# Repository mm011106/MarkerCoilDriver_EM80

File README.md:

> [!NOTE]
> 資料などについてコメント等あればDiscussionsに投稿ください。

# 機器名
## マーカコイルドライバ　EM-80D, EM-80R

# 機器の概要
マーカコイルドライバは、MEG計測時に被験者の頭部位置を推定するための信号を発生させる回路です。被験者の頭部に取り付けた小型コイル（マーカコイル）を既知の周波数で駆動し、発生した磁場をMEGで測定することで頭部位置を特定します。

# 構成 
<!-- この装置は、コイル駆動を行う（型式：EM-80D）とそれをコントロールするためのリモコン（型式：EM-80R）の2つの筐体に入った回路で構成されています。 </br>
コイル駆動回路は、MEG計測への電磁的影響を最小限にするためバッテリ（単３ｘ４）で駆動するように設計されています。また、リモコンはMEG装置と接続され、MEG装置からのコイル駆動動作のOn/Off操作を受け付けたり、MEG装置へコイルの駆動タイミング情報を送る役割を果たします。 </br>
両者はプラスティック光ファイバで接続され、シールドルーム外からの電磁的なノイズ流入を最小限に抑えます。 リモコン→コイル駆動回路への信号はパルス幅変調による1bitの情報で、EM-80Dの動作モードの変更を行います。コイル駆動回路→リモコンへの信号はコイル駆動のタイミング同期信号となっています。</br>
-->
この装置は、コイル駆動回路（型式：EM-80D）と、そのコントロール用リモコン（型式：EM-80R）の2つの筐体で構成されています。</br>
コイル駆動回路はシールドルーム内部に設置されるため、MEG計測への電磁的影響を最小限に抑える目的でバッテリ（単3×4）で駆動されます。</br>
リモコンはシールドルームの外でMEG装置と接続され、コイル駆動のOn/Off操作や駆動タイミング情報をMEG装置に送信します。</br>
両者はプラスチック光ファイバで接続され、シールドルーム外から電磁的ノイズの侵入を抑制します。</br>
リモコンからコイル駆動回路への信号はコイル駆動回路の動作モードを変更のためのパルス幅変調による1bitの情報です。一方、コイル駆動回路からリモコンへはコイル駆動タイミングの同期信号が送出されます。</br>
マーカコイルそのものについては、この設計情報に含まれません。

# 動作の概要
本装置は3つの状態があり、それぞれ「スタンバイモード」「80Hzモード」「ReTHMモード」と呼びます。

## スタンバイモード
スタンバイモードはコイルを駆動していない状態です。EM-80Dの電源スイッチを投入した直後の初期状態のモードになります。</br>
内部回路は動作しており、光ファイバを経由した外部からの動作指示を待ちます。

## 80Hzモード
5個のコイルをシーケンシャルに駆動するモードです。</br>
励磁の周波数は80Hzで、[このシーケンス](#コイル駆動のタイミングチャート)のようにコイルが駆動されます。シーケンスの最初に光ファイバ上に同期信号が出力され順次5個のコイルが駆動されます。</br>
コイルの駆動電流はEM-80Dのリアパネルにあるトグルスイッチ2つで設定できます。</br>

## ReTHMモード
5個のコイルをそれぞれ異なる周波数で同時に駆動するモードです。</br>
コイルの励磁周波数は、脳からの生体時期信号の周波数帯域から外れて高く設定されており、脳磁計測中にリアルタイムに頭部位置を検出するのに適しています。</br>
コイルの駆動電流はEM-80Dのリアパネルにあるトグルスイッチ2つで設定できます。

# 仕様
## EM-80D　マーカコイルドライバ （本体）
- ドライブコイル数：5
<br></br>
- 駆動電流 　(リアパネルスイッチによる　4点切り替え)
  - 5/10/50/100μAo-p 	（80Hzモード）
  - 3/6/10/20μAo-p　	（ReTHMモード）
<br></br>
- 動作モード （スタンバイモード/80Hzモード/ReTHMモード）
  - スタンバイモード</br>
    （コイル駆動なし）
<br></br>
  - 80Hzモード
    - 駆動波形：24波のバースト波による順次駆動（[下図参照](#コイル駆動のタイミングチャート)）
    - 駆動周波数：80Hz(typ)
<br></br>
  - ReTHMモード
    - 駆動波形：連続波
    - 駆動周波数 </br>
    CH0	20kHz </br>
    CH1	18kHz </br>
    CH2	16kHz </br>
    CH3	14kHz </br>
    CH4	12kHz
<br></br>

- 動作モード切替 </br>
    リモートコントローラEM-80Rからの信号による（光ファイバ経由）
<br></br>
- インターフェイス </br>
  プラスティック光ファイバ2本による（EM-80Rとの接続専用）
  - 入力信号：駆動モード切替
  - 出力信号：同期信号（80Hzモード時のみ）
<br></br>
- 操作：フロントパネルトグルスイッチによる電源のOn/Off
<br></br>
- 表示：電源電圧低下警告 Low-Battery（LED:赤）
<br></br>
- 電源：単三充電池（Ni-MH）4本
<br></br>
<br></br>
## EM-80R　リモートコントローラ
- 操作
  - フロントパネルトグルスイッチによる駆動モードの変更
  - 外部インターフェイスからの信号による駆動モードの変更
<br></br>
- 表示：LED（緑）によるEM-80Dの駆動モード表示 </br>
    　消灯　　スタンバイモード </br>
    　点滅　　80Hzモード動作中 </br>
    　点灯　　ReTHMモード動作中 </br>
<br></br>
- 外部（MEG装置）インターフェイス
  - 入力2bit（on命令、off命令　各1bit）
  - 出力1bit（同期信号）
  - コネクタ型式：HR10G-10R-10P（ヒロセ）（[ピンアサイン](#meg接続用コネクタピン配置)）
<br></br>
- 電源</br>
  - +5V、100mA以下（microUSBコネクタによる）
<br></br><br></br>
## 動作に必要なもの
- 単三充電池（Ni-MH）4本
- EM-80D ~ EM-80R間接続用光ファイバケーブル
- EM-80R用電源:　USB電源 (5V)もしくはパソコンのUSB端子 と USB-microケーブル
<br></br>

## コイル駆動のタイミングチャート
<!--  -->

## ブロック図
### EM-80D

</br>
</br>
</br>

### EM-80R

</br>
</br>
</br>

## MEG接続用コネクタ　ピン配置
- コネクタ型番：[HR10G-10R-10P73](https://www.hirose.com/ja/product/p/CL0110-1608-0-73#) ヒロセ（レセプタクル）

### MEG接続用コネクタのフォトカプラ周辺回路

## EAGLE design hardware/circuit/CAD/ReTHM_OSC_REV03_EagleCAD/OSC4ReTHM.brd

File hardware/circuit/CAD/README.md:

# このディレクトリについて
このディレクトリは回路図CADのプロジェクトが保管されています。</br>
使用したCADは　CadSoft Eagle バージョン7.4　です。</br>

## 構成
[本体](./EM-80DR_REV06_EagleCAD)のCADデータは、EM-80Dマーカコイルドライバ本体と、EM-80Rリモートコントローラの2つの設計が1つのプロジェクトとして登録されています。基板データは2つの設計が面付されています。</br>
本体回路のほかに、本体内部で使用するワイヤハーネスの設計図も入っています。

[ReTHM_OSC](./ReTHM_OSC_REV03_EagleCAD)のCADデータは、内蔵するReTHMモード用の発振回路の設計がプロジェクトとして登録されています。</br>
ReTHM発振回路は5種類の周波数設定があります。基板は同じで回路定数を変更して5種類の発振周波数を実現します。

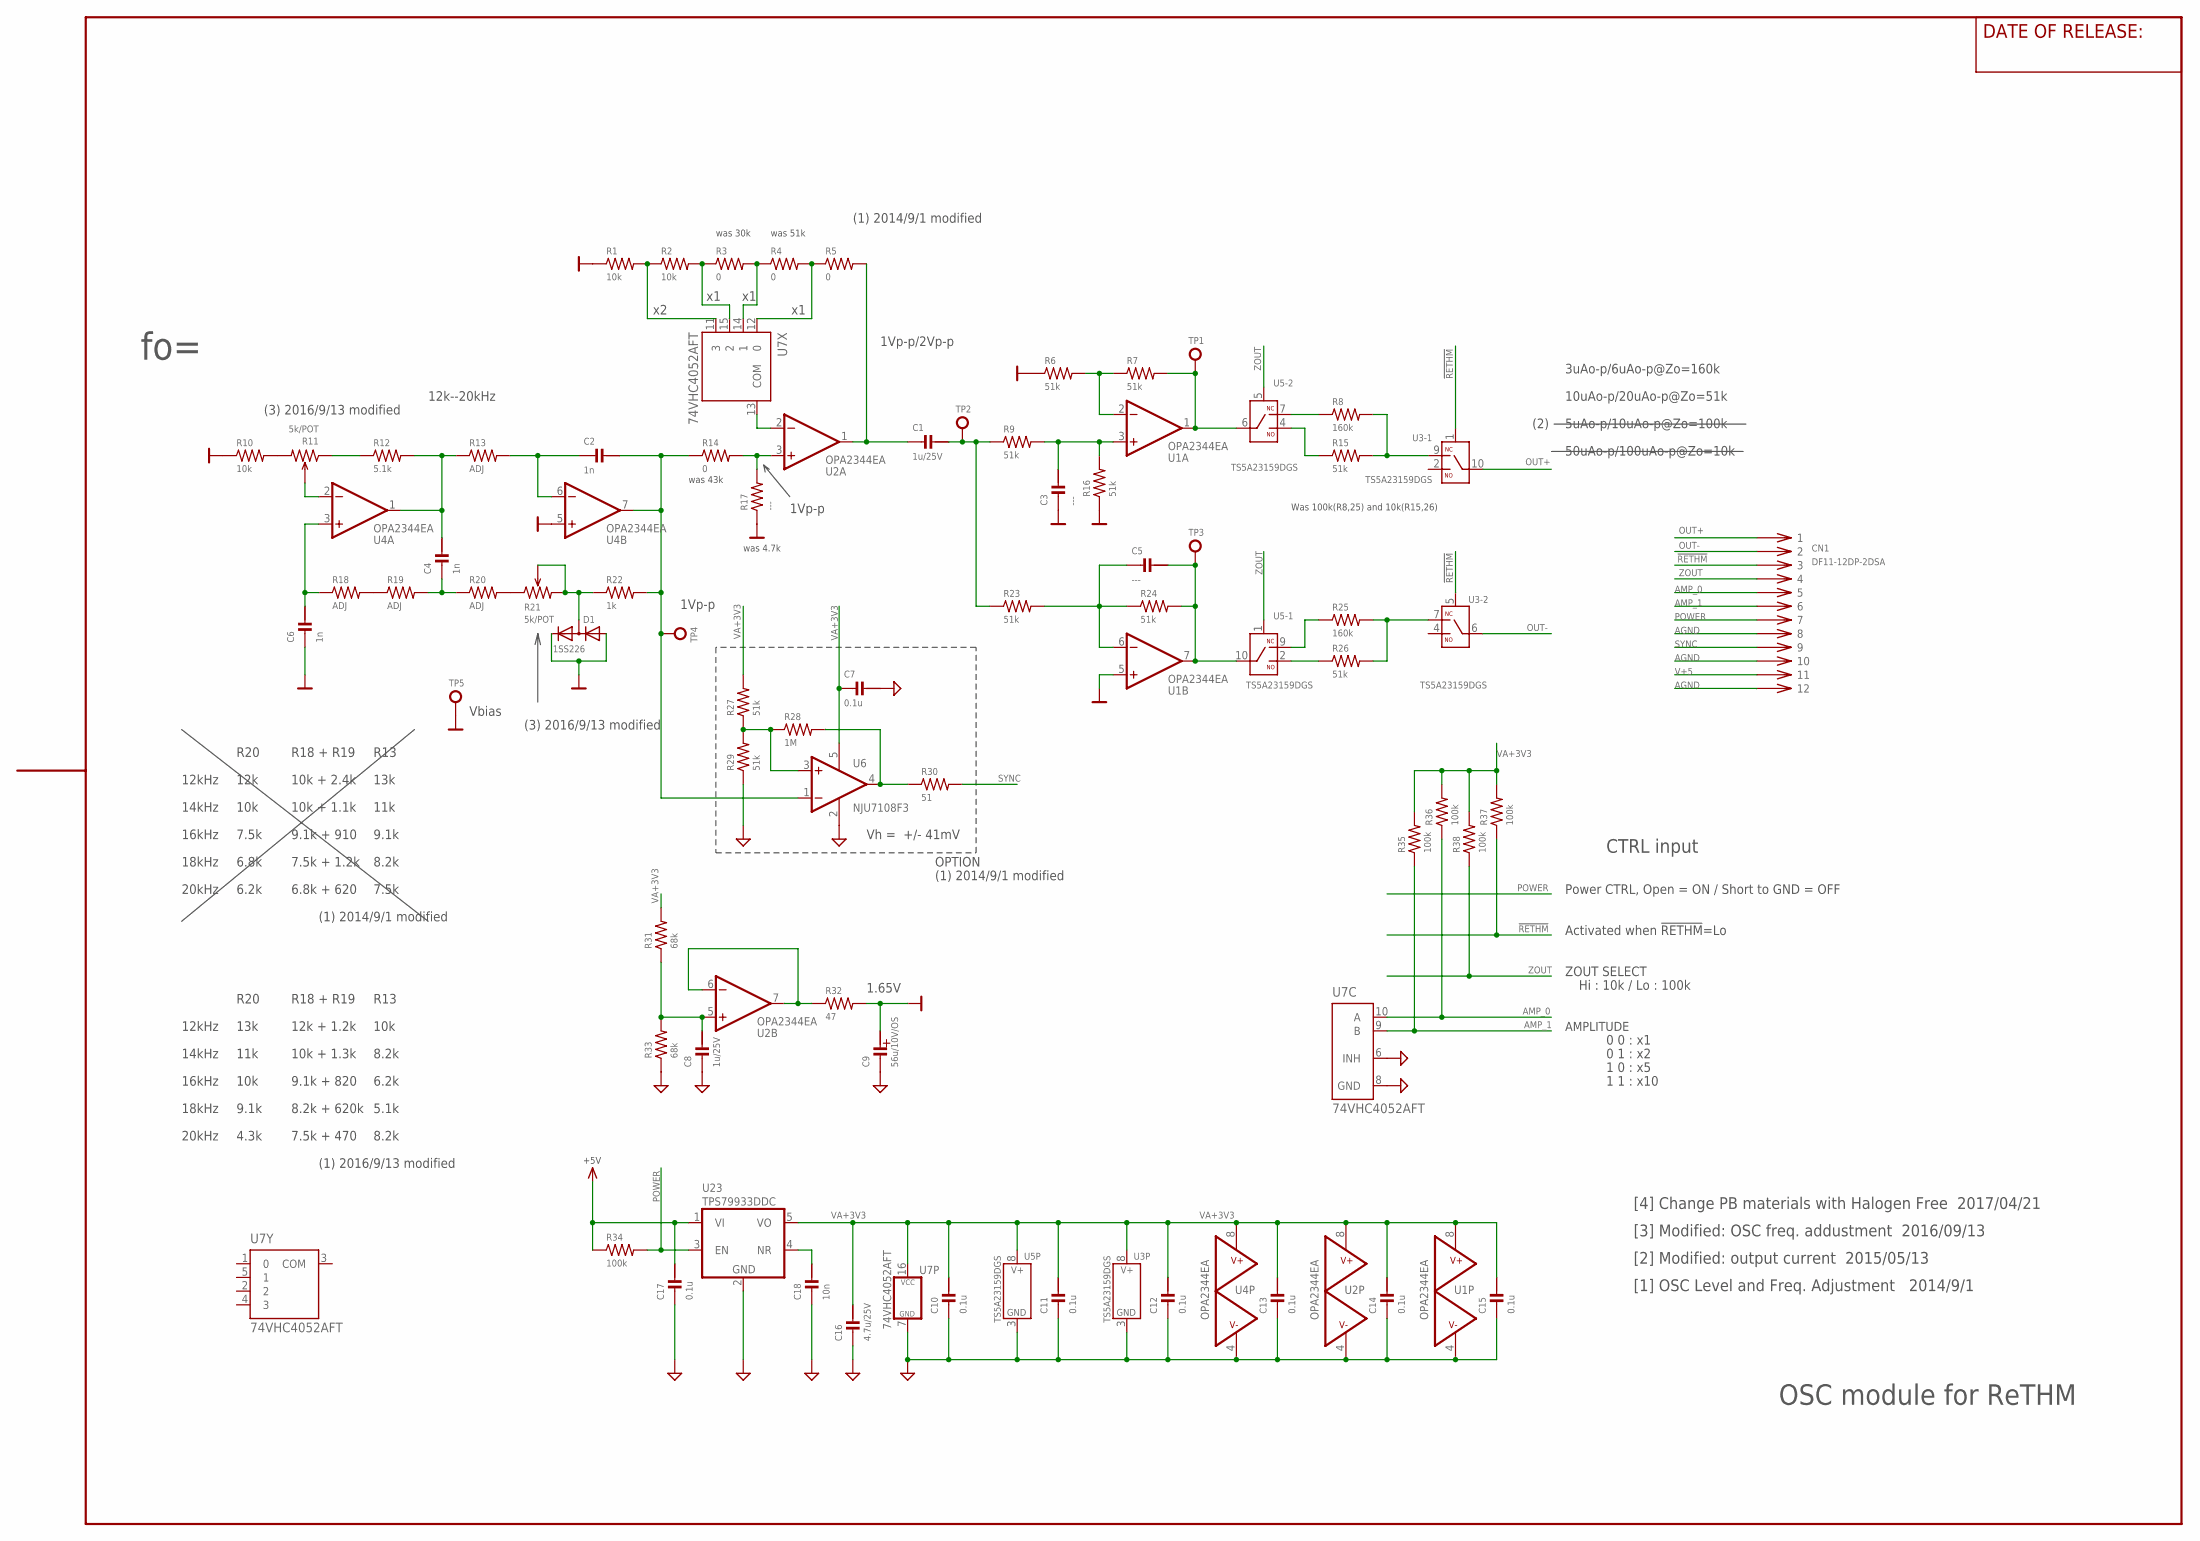
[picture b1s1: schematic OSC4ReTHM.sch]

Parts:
C1, C8: 1u/25V; CM1608
C2, C4, C6: 1n; CM2012
C3, C5: ---; CM2012
C7, C10, C11, C12, C13, C14, C15, C17: 0.1u; CM1608
C9: 56u/10V/OS; PHI_6.3
C16: 4.7u/25V; CM2012
C18: 10n; CM2012
CN1: DF11-12DP-2DSA
D1: 1SS226; SOT23
R1, R2, R10: 10k; RM1608
R3, R4, R5, R14: 0; RM1608
R6, R7, R9, R15, R16, R23, R24, R26, R27, R29: 51k; RM1608
R8, R25: 160k; RM1608
R11, R21: 5k/POT; CT-6
R12: 5.1k; RM1608
R13, R18, R19, R20: ADJ; RM1608
R17: ---; RM1608
R22: 1k; RM1608
R28: 1M; RM1608
R30: 51; RM1608
R31, R33: 68k; RM1608
R32: 47; RM1608
R34, R35, R36, R37, R38: 100k; RM1608
TP1, TP3, TP5: TP-1PAD; TP_PAD_1MM
TP2, TP4: TP-LC3G; TP_TH_0R9MM
U1, U2, U4: OPA2344EA; MSO8_AEL
U3, U5: TS5A23159DGS; MSOP10
U6: NJU7108F3; SC88A
U7: 74VHC4052AFT; TSSOP16-P-044-065A
U23: TPS79933DDC; SOT-23-5

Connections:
0V: C3.2, C6.2, C9.POS, D1.1 (A), D1.2 (C), R1.1, R6.1, R10.1, R16.1, R17.1, R32.2, TP5.P$1, U1.5 (+IN), U4.5 (+IN)
!RETHM: CN1.3, R37.1, U3.1 (IN), U3.5 (IN)
AGND: C7.1, C8.2, C9.NEG, C10.2, C11.2, C12.2, C13.2, C14.2, C15.2, C16.2, C17.2, C18.2, CN1.8, CN1.10, CN1.12, R29.1, R33.1, U1.4 (V-), U2.4 (V-), U3.3 (V-), U4.4 (V-), U5.3 (V-), U6.2 (V-), U7.6 (INH), U7.7 (GND), U7.8 (GND), U23.2 (GND)
AMP_0: CN1.5, R36.1, U7.10 (A)
AMP_1: CN1.6, R35.1, U7.9 (B)
unnamed: R20.2, R21.1
unnamed: R10.2, R11.3
unnamed: C18.1, U23.4 (NR)
unnamed: R1.2, R2.1, U7.11 (3)
unnamed: R2.2, R3.1, U7.15 (2)
unnamed: R3.2, R4.1, U7.14 (1)
unnamed: R4.2, R5.1, U7.12 (0)
unnamed: C8.1, R31.1, R33.2, U2.5 (+IN)
unnamed: C5.2, R23.2, R24.1, U1.6 (-IN)
unnamed: U2.2 (-IN), U7.13 (COM)
unnamed: C1.2, R5.2, U2.1 (OUT)
unnamed: R14.2, R17.2, U2.3 (+IN)
unnamed: C5.1, R24.2, TP3.P$1, U1.7 (OUT), U5.10 (COM)
unnamed: R7.2, TP1.P$1, U1.1 (OUT), U5.6 (COM)
unnamed: R6.2, R7.1, U1.2 (-IN)
unnamed: C3.1, R9.2, R16.2, U1.3 (+IN)
unnamed: R26.1, U5.2 (NO)
unnamed: R25.1, U5.9 (NC)
unnamed: R25.2, R26.2, U3.7 (NC)
unnamed: R8.1, U5.7 (NC)
unnamed: R15.1, U5.4 (NO)
unnamed: R8.2, R15.2, U3.9 (NC)
unnamed: R11.1, R12.1
unnamed: C4.1, R12.2, R13.1, U4.1 (OUT)
unnamed: C2.2, R13.2, U4.6 (-IN)
unnamed: C2.1, R14.1, R22.2, TP4.1, U4.7 (OUT), U6.1 (-IN)
unnamed: R11.2, U4.2 (-IN)
unnamed: C6.1, R18.1, U4.3 (+IN)
unnamed: R18.2, R19.1
unnamed: C4.2, R19.2, R20.1
unnamed: D1.3 (AC), R21.2, R21.3, R22.1
unnamed: C1.1, R9.1, R23.1, TP2.1
unnamed: R32.1, U2.6 (-IN), U2.7 (OUT)
unnamed: R27.1, R28.1, R29.2, U6.3 (+IN)
unnamed: R28.2, R30.1, U6.4 (OUT)
OUT+: CN1.1, U3.10 (COM)
OUT-: CN1.2, U3.6 (COM)
POWER: CN1.7, R34.2, U23.3 (EN)
SYNC: CN1.9, R30.2
V+5: C17.1, CN1.11, R34.1, U23.1 (VI)
VA+3V3: C7.2, C10.1, C11.1, C12.1, C13.1, C14.1, C15.1, C16.1, R27.2, R31.2, R35.2, R36.2, R37.2, R38.2, U1.8 (V+), U2.8 (V+), U3.8 (V+), U4.8 (V+), U5.8 (V+), U6.5 (V+), U7.16 (VCC), U23.5 (VO)
ZOUT: CN1.4, R38.1, U5.1 (IN), U5.5 (IN)

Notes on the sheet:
OSC module for ReTHM
CTRL input
AMPLITUDE
ZOUT SELECT
Hi : 10k / Lo : 100k
0 0 : x1
0 1 : x2
1 0 : x5
1 1 : x10
1.65V
Vh = +/- 41mV
Vbias
1Vp-p
12k--20kHz
Activated when !RETHM!=Lo
Power CTRL, Open = ON / Short to GND = OFF
R20
12kHz
14kHz
16kHz
18kHz
20kHz
12k
10k
7.5k
6.8k
6.2k
R18 + R19
10k + 2.4k
10k + 1.1k
9.1k + 910
7.5k + 1.2k
6.8k + 620
R13
13k
11k
9.1k
8.2k
(1) 2014/9/1 modified
OPTION

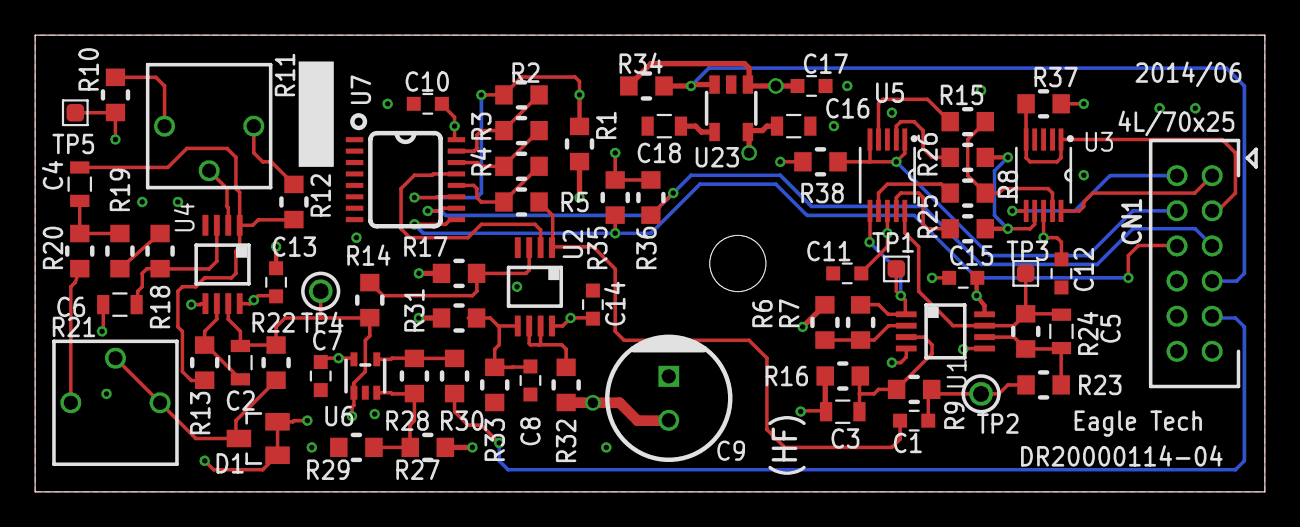
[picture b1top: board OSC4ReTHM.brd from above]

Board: 4 copper layers, 70.0 x 26.0 mm, 71 parts (0 on the bottom side), 47 nets.

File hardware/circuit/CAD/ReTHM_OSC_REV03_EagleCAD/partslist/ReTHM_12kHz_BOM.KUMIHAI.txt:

-NO_WORK- (---)	 3	 C3 C5 R17
-NO_WORK- (TP-1PAD)	 3	 TP1 TP3 TP5
10SEP56 (56u/10V/OS)	 1	 C9
1SS226 (1SS226)	 1	 D1
CT-6EP5kohm (5k/POT)	 2	 R11 R21
DF11-12DP-2DSA(24) (DF11-12DP-2DSA)	 1	 CN1
GRM1882C1H102J (1n)	 3	 C2 C4 C6
GRM188B31E105K (1u/25V)	 2	 C1 C8
GRM188B31H104K (0.1u)	 7	 C10 C11 C12 C13 C14 C15 C17
GRM2192C1H103J (10n)	 1	 C18
GRM21BB31E475K (4.7u/25V)	 1	 C16
LC-3-G (TP-LC3G)	 2	 TP2 TP4
OPA2344EA (OPA2344EA)	 3	 U1 U2 U4
RMC1/16JP (0)	 4	 R3 R4 R5 R14
RMC1/16K470F (47)	 1	 R32
RR0816P-102-D (1k)	 1	 R22
RR0816P-103-D (10k)	 4	 R1 R2 R10 R20
RR0816P-104-D (100k)	 5	 R34 R35 R36 R37 R38
RR0816P-122-D (1.2k)	 1	 R19
RR0816P-123-D (12k)	 1	 R18
RR0816P-133-D (13k)	 1	 R13
RR0816P-164-D (160k)	 2	 R8 R25
RR0816P-512-D (5.1k)	 1	 R12
RR0816P-513-D (51k)	 8	 R6 R7 R9 R15 R16 R23 R24 R26
RR0816P-683-D (68k)	 2	 R31 R33
TC74VHC4052AFT (74VHC4052AFT)	 1	 U7
TPS79933DDC (TPS79933DDC)	 1	 U23
TS5A23159DGS (TS5A23159DGS)	 2	 U3 U5

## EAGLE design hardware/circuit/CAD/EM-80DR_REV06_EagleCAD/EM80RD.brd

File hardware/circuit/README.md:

# このディレクトリについて

このディレクトリにはPDF版の回路図とその元となるCADデータ（EagleCAD-Fusionフォーマット）を保管しています。

## 回路図

- [EM80DR_SCH_10.pdf](EM80DR_SCH_10.pdf)</br>
    マーカコイルドライバとそのリモコンの回路図です。</br>
    CPLDを使っていますが、その設計については[こちら](../../software/HDL)を参照してください。
  
- [OPTFIBER_harnessAssy_REV01.pdf](OPTFIBER_harnessAssy_REV01.pdf)</br>
    プラスティック光ファイバの回路図（仕様書）です。長さ10mですが、適宜状況に応じて変更してください。長くした場合、ファイバ内での光の減衰により通信が不安定になる可能性がありますので、マーカコイルドライバ本体、リモコン回路のトランスミッタICの駆動電流を調整してください。

- OSC4ReTHM_12kHz.pdf ~ OSC4ReTHM_20kHz.pdf </br>
    ReTHMモードでの励磁用発振回路です。

- [Remote_harnessAssy.pdf](Remote_harnessAssy.pdf)</br>
    EM-80R内部のワイヤハーネスの回路図です。

- [design_note.md](design_note.md)</br>
    回路設計の詳細について解説しています。

## CADデータ
CADのプロジェクトファイルとそこから生成した基板製造用のガーバデータがあります。</br>
CADのプロジェクトファイルは2つあり、1つがマーカコイルドライバ本体・リモコン、もう一つがReTHM用発信回路です。

ガーバデータにはハンダマスク、マウントデータは含まれていませんので必要に応じて作成してください。

回路図・PCBのデータは **Eagle CAD 7.4** にて作成しています。

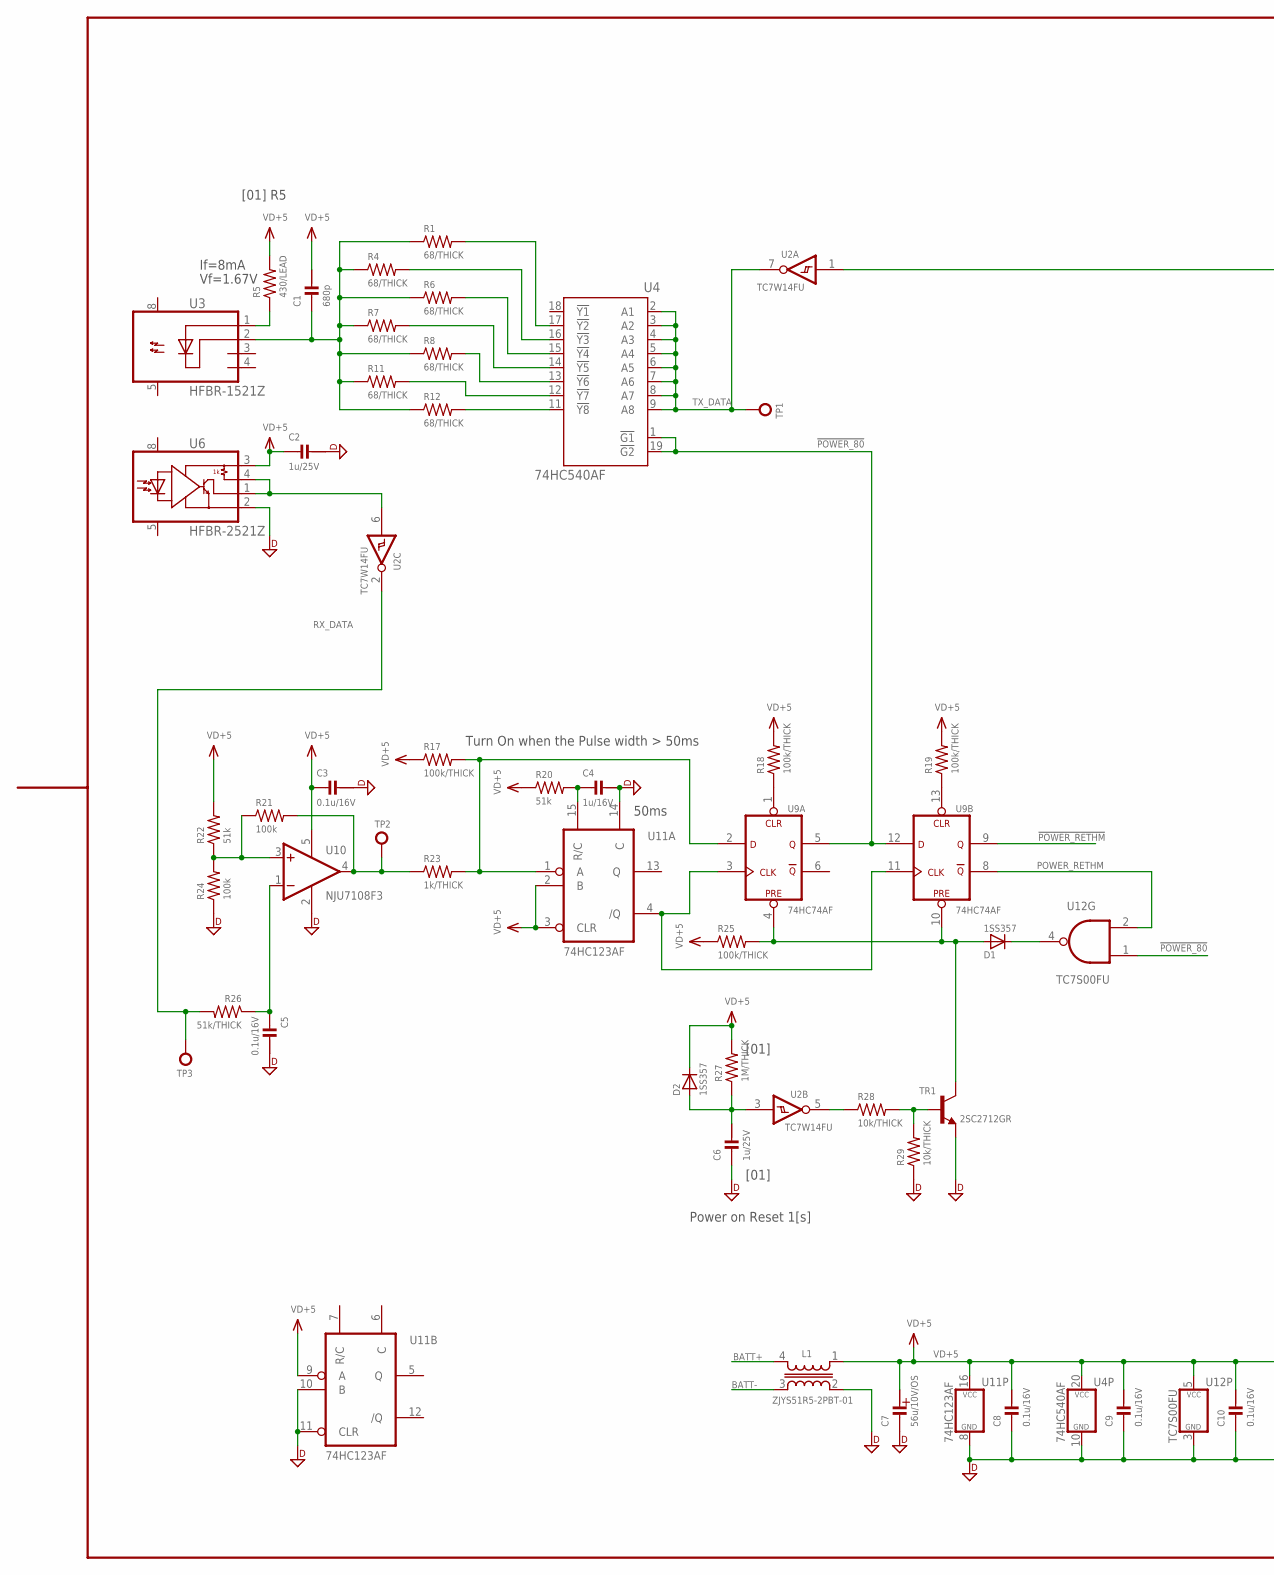
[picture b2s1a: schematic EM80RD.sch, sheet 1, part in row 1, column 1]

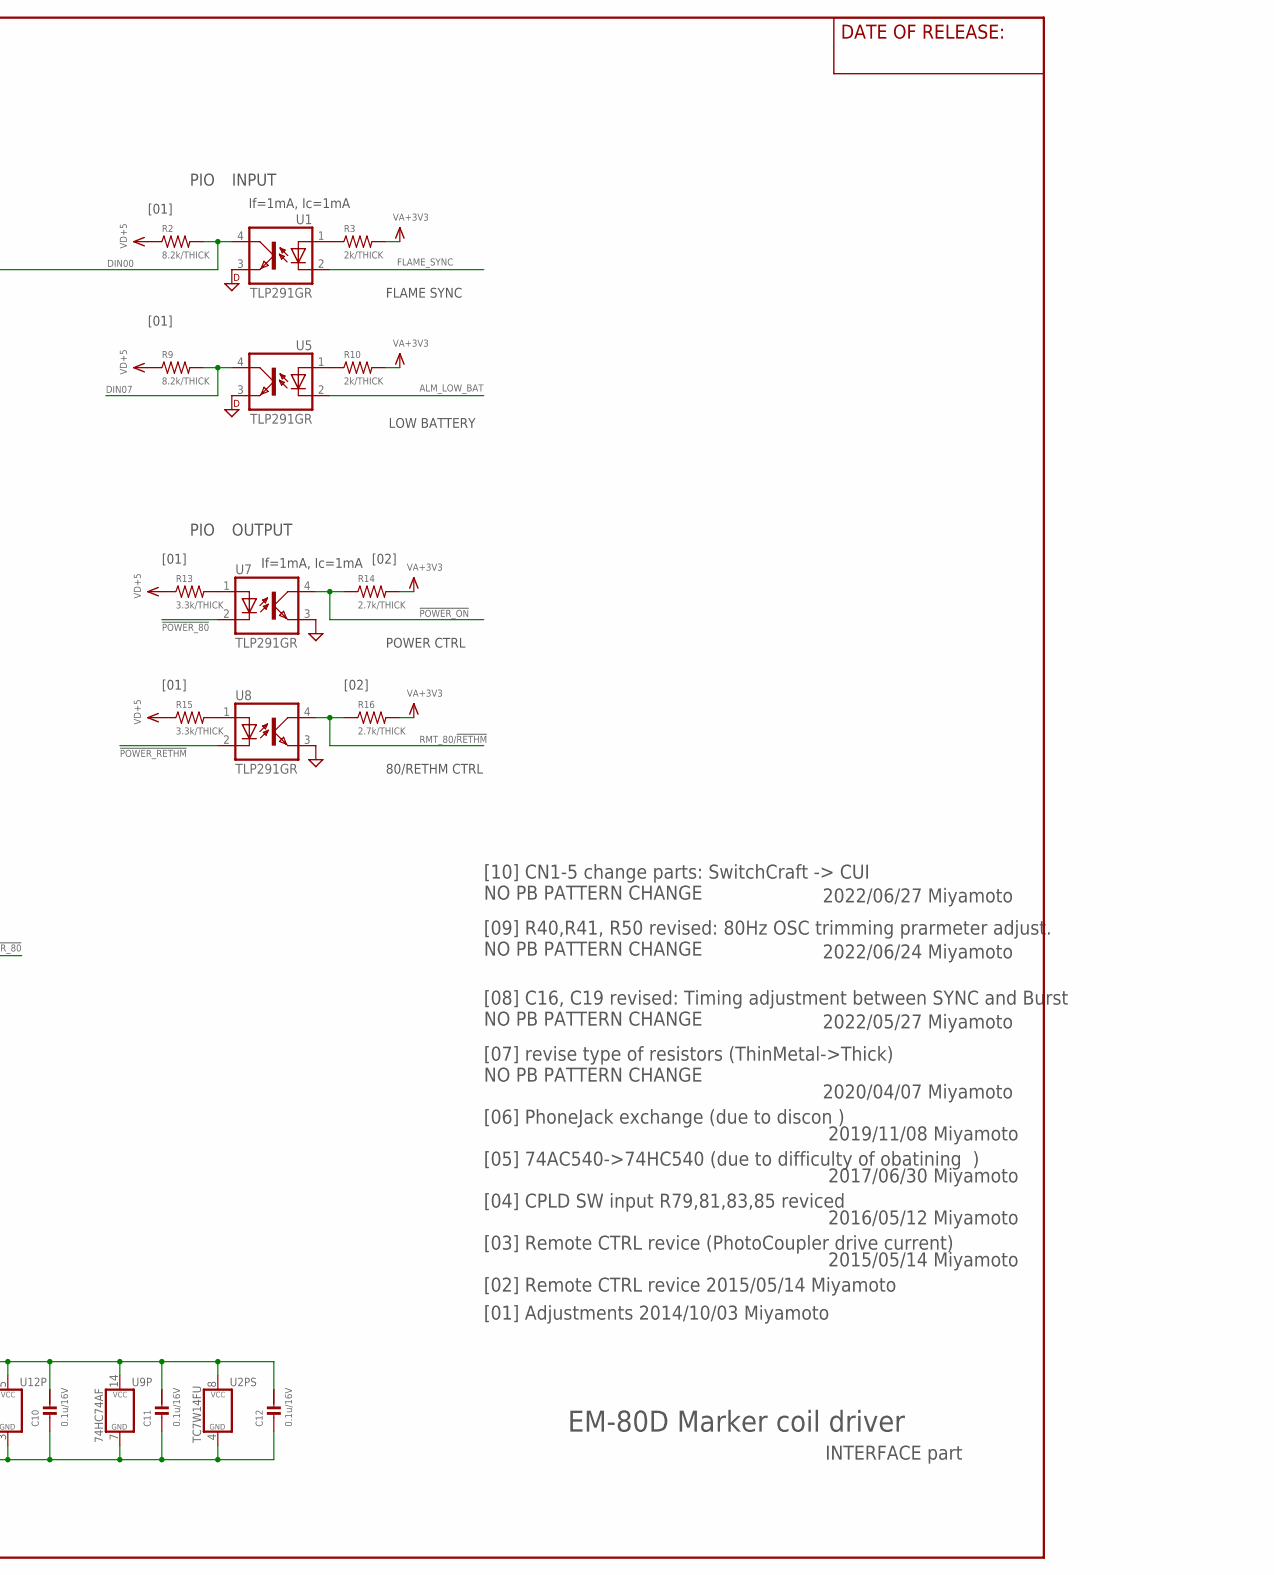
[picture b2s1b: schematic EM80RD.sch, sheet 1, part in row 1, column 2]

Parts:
C1: 680p; CM1608
C2: 1u/25V; CM2012
C3, C5, C8, C9, C10, C11, C12: 0.1u/16V; CM1608
C4: 1u/16V; CM2012
C6: 1u/25V; CM1608
C7: 56u/10V/OS; PHI_6.3
D1, D2: 1SS357; SOD323-R
L1: ZJYS51R5-2PBT-01; ZJYS51-2
R1, R4, R6, R7, R8, R11, R12: 68/THICK; RM1608
R2, R9: 8.2k/THICK; RM1608
R3, R10: 2k/THICK; RM1608
R5: 430/LEAD; 0207/2V
R13, R15: 3.3k/THICK; RM1608
R14, R16: 2.7k/THICK; RM1608
R17, R18, R19, R25: 100k/THICK; RM1608
R20, R22: 51k; RM1608
R21, R24: 100k; RM1608
R23: 1k/THICK; RM1608
R26: 51k/THICK; RM1608
R27: 1M/THICK; RM1608
R28, R29: 10k/THICK; RM1608
TP1, TP2, TP3: TP-LC3G; TP_TH_0R9MM
TR1: 2SC2712GR; SOT23-BEC
U1, U5, U7, U8: TLP291GR; SO4(11-3C1)(TOSHIBA)
U2: TC7W14FU; SSOP8-P-065
U3: HFBR-1521Z; HFBR-X52X
U4: 74HC540AF; SO20_300MIL
U6: HFBR-2521Z; HFBR-X52X
U9: 74HC74AF; SO14_300MIL
U10: NJU7108F3; SC88A
U11: 74HC123AF; SO16_300MIL
U12: TC7S00FU; SSOP5-P-065A(USV)

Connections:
!POWER_80: U4.1 (!G1), U4.19 (!G2), U7.2 (C), U9.5 (Q), U9.12 (D), U12.1 (I1)
!POWER_ON: R14.1, U7.4 (COL); also elsewhere on the board
!POWER_RETHM: U8.2 (C), U9.9 (Q)
AGND: U7.3 (EMI), U8.3 (EMI); also elsewhere on the board
ALM_LOW_BAT: U5.2 (C); also elsewhere on the board
BATT+: L1.4 (1); also elsewhere on the board
BATT-: L1.3; also elsewhere on the board
DGND: C2.1, C3.1, C4.1, C5.1, C6.2, C7.NEG, C8.2, C9.2, C10.2, C11.2, C12.2, L1.2 (4), R24.1, R29.1, TR1.E, U1.3 (EMI), U2.4 (GND), U4.10 (GND), U5.3 (EMI), U6.2 (GND), U9.7 (GND), U10.2 (V-), U11.8 (GND), U11.10 (B), U11.11 (CLR), U11.14 (C), U12.3 (GND); also elsewhere on the board
DIN00: R2.2, U1.4 (COL), U2.1 (I)
DIN07: R9.2, U5.4 (COL)
FLAME_SYNC: U1.2 (C); also elsewhere on the board
unnamed: R1.2, U4.17 (!Y2)
unnamed: R6.2, U4.15 (!Y4)
unnamed: R7.2, U4.14 (!Y5)
unnamed: R8.2, U4.13 (!Y6)
unnamed: R11.2, U4.12 (!Y7)
unnamed: R12.2, U4.11 (!Y8)
unnamed: R4.2, U4.16 (!Y3)
unnamed: R21.1, R22.1, R24.2, U10.3 (+IN)
unnamed: R21.2, R23.1, TP2.1, U10.4 (OUT)
unnamed: C5.2, R26.1, U10.1 (-IN)
unnamed: D1.A, R25.2, TR1.C, U9.4 (PRE), U9.10 (PRE)
unnamed: R19.1, U9.13 (CLR)
unnamed: C1.2, R1.1, R4.1, R6.1, R7.1, R8.1, R11.1, R12.1, U3.2 (C)
unnamed: R5.1, U3.1 (A)
unnamed: U2.6 (I), U6.1 (VO), U6.4 (RL)
unnamed: R3.1, U1.1 (A)
unnamed: R10.1, U5.1 (A)
unnamed: U9.3 (CLK), U9.11 (CLK), U11.4 (/Q)
unnamed: C6.1, D2.A, R27.1, U2.3 (I)
unnamed: R13.2, U7.1 (A)
unnamed: R15.2, U8.1 (A)
unnamed: R18.1, U9.1 (CLR)
unnamed: C4.2, R20.2, U11.15 (R/C)
unnamed: D1.C, U12.4 (O)
unnamed: R28.1, U2.5 (O)
unnamed: R28.2, R29.2, TR1.B
POWER_RETHM: U9.8 (!Q), U12.2 (I0)
PWR_ON: R17.2, R23.2, U9.2 (D), U11.1 (A)
RMT_80/!RETHM: R16.1, U8.4 (COL); also elsewhere on the board
RX_DATA: R26.2, TP3.1, U2.2 (O)
TX_DATA: TP1.1, U2.7 (O), U4.2 (A1), U4.3 (A2), U4.4 (A3), U4.5 (A4), U4.6 (A5), U4.7 (A6), U4.8 (A7), U4.9 (A8)
VA+3V3: R3.2, R10.2, R14.2, R16.2; also elsewhere on the board
VD+5: C1.1, C2.2, C3.2, C7.POS, C8.1, C9.1, C10.1, C11.1, C12.1, D2.C, L1.1 (2), R2.1, R5.2, R9.1, R13.1, R15.1, R17.1, R18.2, R19.2, R20.1, R22.2, R25.1, R27.2, U2.8 (VCC), U4.20 (VCC), U6.3 (VCC), U9.14 (VCC), U10.5 (V+), U11.2 (B), U11.3 (CLR), U11.9 (A), U11.16 (VCC), U12.5 (VCC)

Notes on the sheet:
If=8mA
Vf=1.67V
EM-80D Marker coil driver
PIO
INPUT
OUTPUT
FLAME SYNC
LOW BATTERY
POWER CTRL
80/RETHM CTRL
50ms
Turn On when the Pulse width > 50ms
If=1mA, Ic=1mA
INTERFACE part
[01] Adjustments 2014/10/03 Miyamoto
[01] R5
[01]
[02]
Power on Reset 1[s]
[02] Remote CTRL revice 2015/05/14 Miyamoto
[03] Remote CTRL revice (PhotoCoupler drive current)
2015/05/14 Miyamoto
[04] CPLD SW input R79,81,83,85 reviced
2016/05/12 Miyamoto
[05] 74AC540->74HC540 (due to difficulty of obatining )
2017/06/30 Miyamoto
[06] PhoneJack exchange (due to discon )
2019/11/08 Miyamoto
[07] revise type of resistors (ThinMetal->Thick) NO PB PATTERN CHANGE
2020/04/07 Miyamoto
[08] C16, C19 revised: Timing adjustment between SYNC and Burst NO PB PATTERN CHANGE
2022/05/27 Miyamoto
2022/06/24 Miyamoto
[09] R40,R41, R50 revised: 80Hz OSC trimming prarmeter adjust. NO PB PATTERN CHANGE
[10] CN1-5 change parts: SwitchCraft -> CUI NO PB PATTERN CHANGE
2022/06/27 Miyamoto

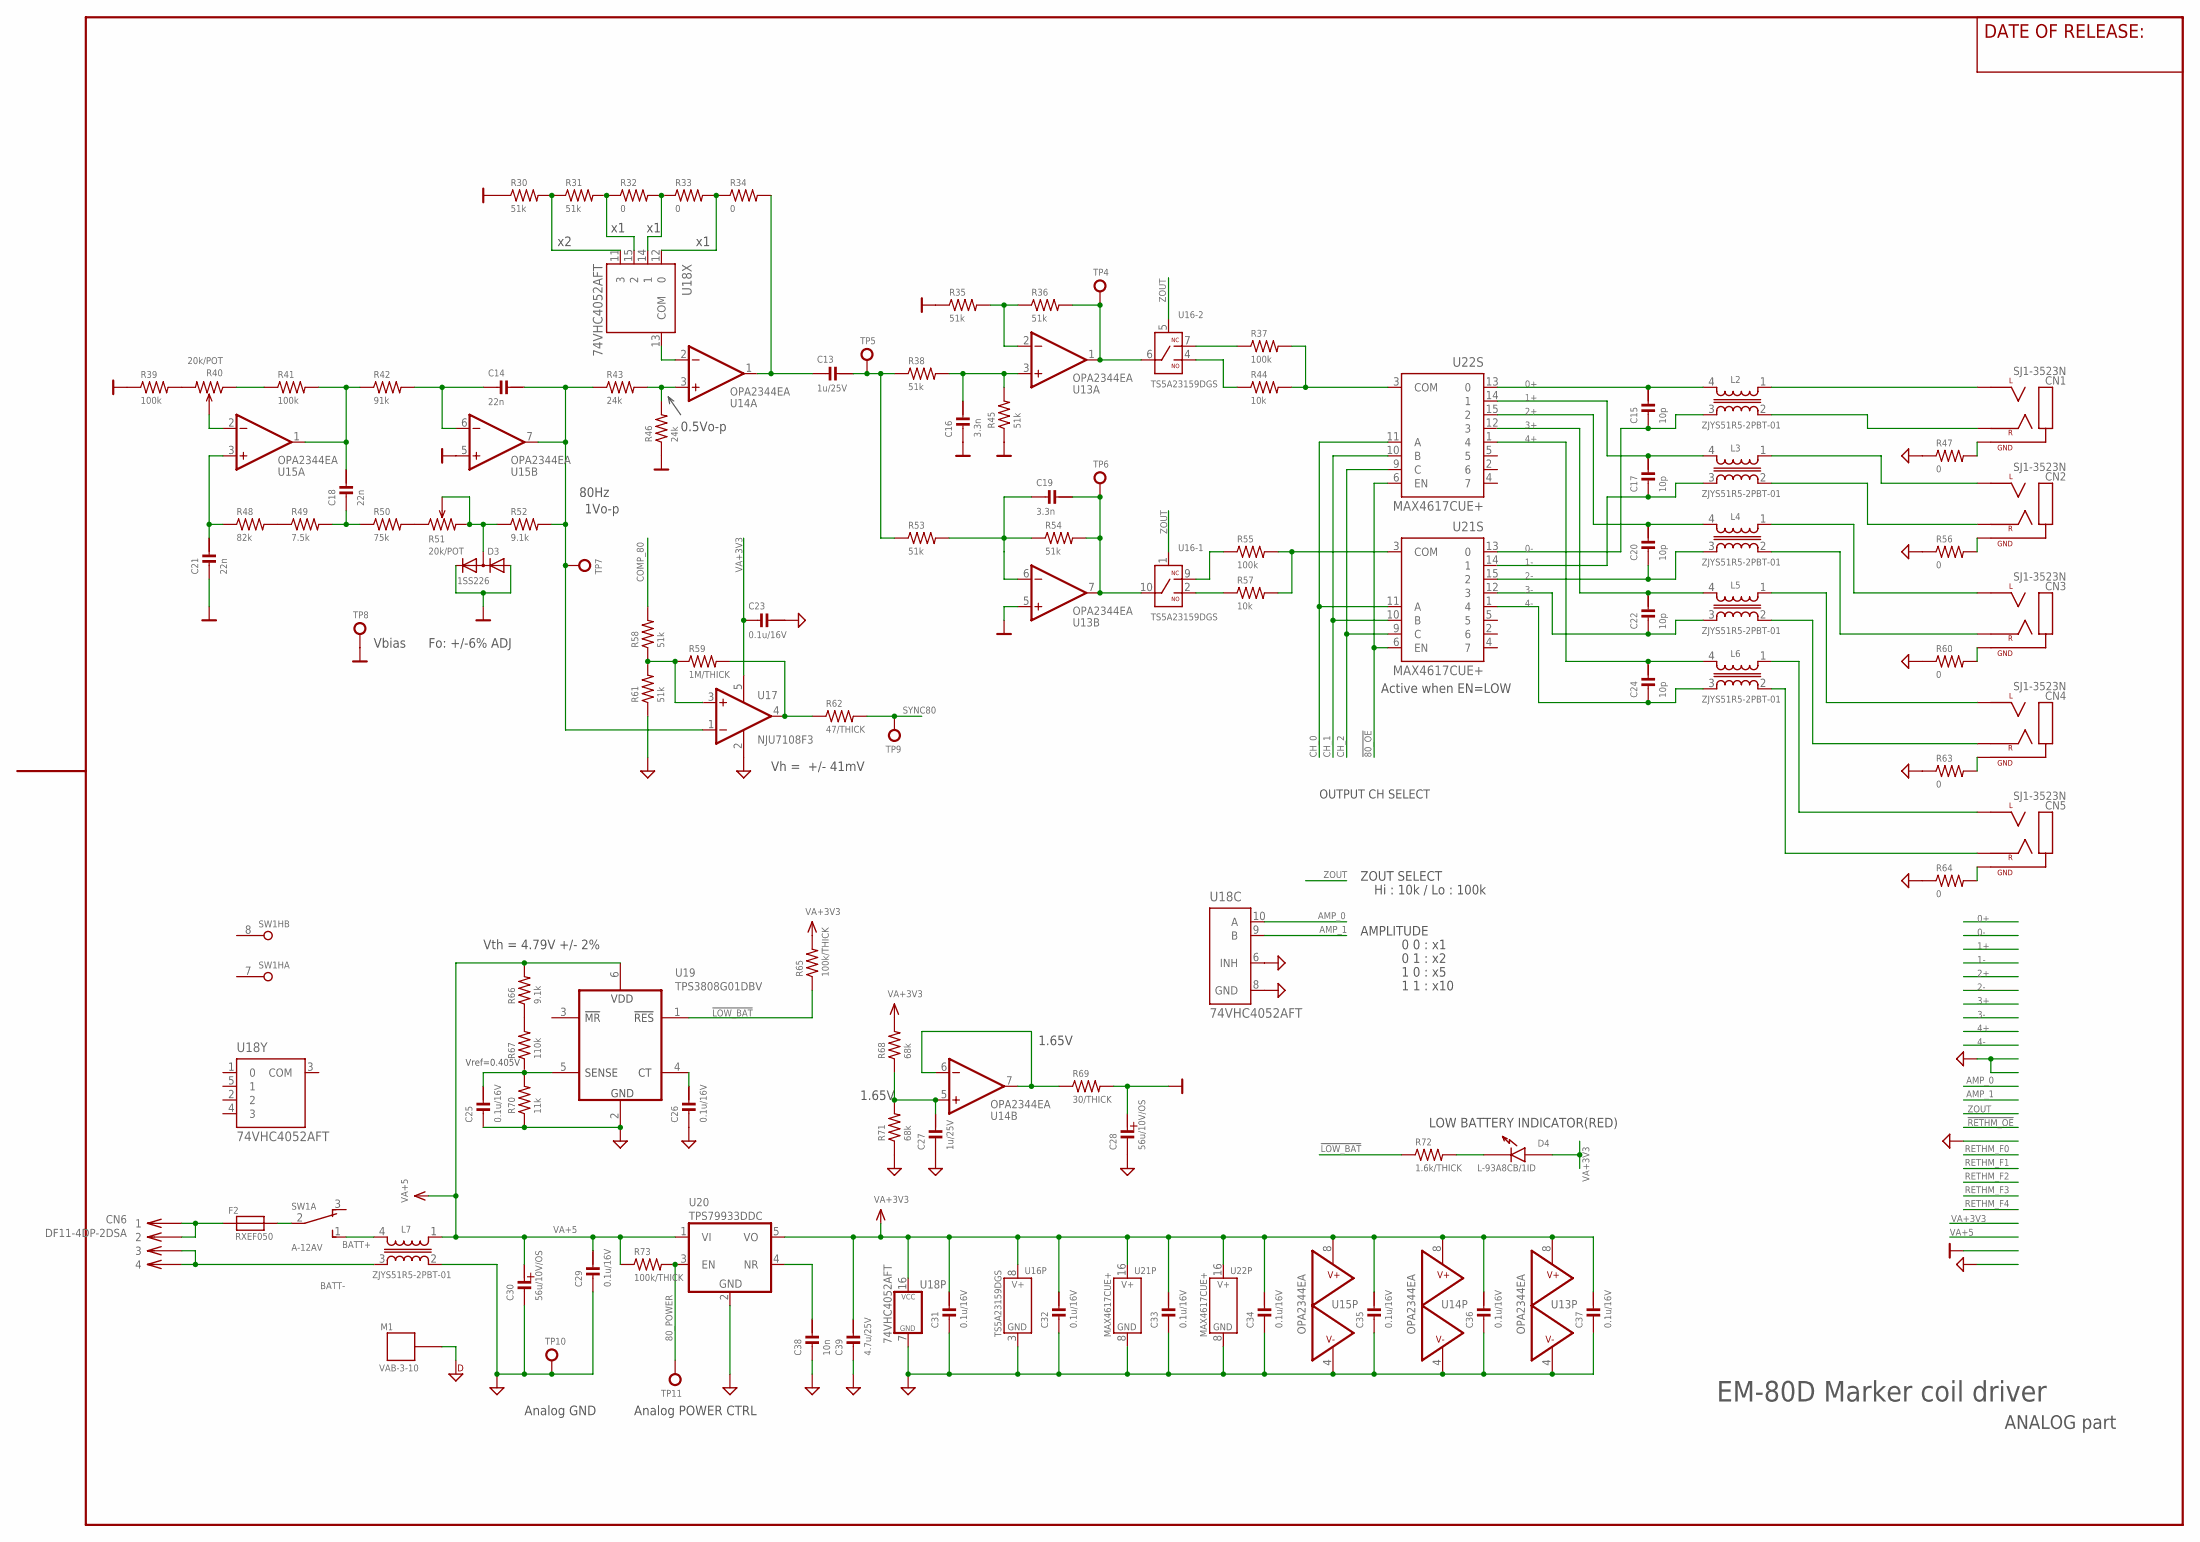
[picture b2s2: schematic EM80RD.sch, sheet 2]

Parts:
C13, C27: 1u/25V; CM1608
C14, C18, C21: 22n; CM3216
C15, C17, C20, C22, C24: 10p; CM1608
C16, C19: 3.3n; CM2012
C23, C25, C26, C29, C31, C32, C33, C34, C35, C36, C37: 0.1u/16V; CM1608
C28, C30: 56u/10V/OS; PHI_6.3
C38: 10n; CM2012
C39: 4.7u/25V; CM2012
CN1, CN2, CN3, CN4, CN5: SJ1-3523N; 35RAPC2BHN2
CN6: DF11-4DP-2DSA
D3: 1SS226; SOT23
D4: L-93A8CB/1ID; L-93A8CB
F2: RXEF050; 8X3/5.08
L2, L3, L4, L5, L6, L7: ZJYS51R5-2PBT-01; ZJYS51-2
M1: VAB-3-10; VAB_3_10_CONTACT
R30, R31, R35, R36, R38, R45, R53, R54, R58, R61: 51k; RM1608
R32, R33, R34, R47, R56, R60, R63, R64: 0; RM1608
R37, R39, R41, R55: 100k; RM1608
R40, R51: 20k/POT; CT-6
R42: 91k; RM1608
R43, R46: 24k; RM1608
R44, R57: 10k; RM1608
R48: 82k; RM1608
R49: 7.5k; RM1608
R50: 75k; RM1608
R52, R66: 9.1k; RM1608
R59: 1M/THICK; RM1608
R62: 47/THICK; RM1608
R65, R73: 100k/THICK; RM1608
R67: 110k; RM1608
R68, R71: 68k; RM1608
R69: 30/THICK; RM1608
R70: 11k; RM1608
R72: 1.6k/THICK; RM1608
SW1: A-12AV; A-12*
TP4, TP5, TP6, TP7, TP8, TP9, TP10, TP11: TP-LC3G; TP_TH_0R9MM
U13, U14, U15: OPA2344EA; MSO8_AEL
U16: TS5A23159DGS; MSOP10
U17: NJU7108F3; SC88A
U18: 74VHC4052AFT; TSSOP16-P-044-065A
U19: TPS3808G01DBV; SOT-23
U20: TPS79933DDC; SOT-23-5
U21, U22: MAX4617CUE+; TSSOP16_AEL

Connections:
0+: C15.1, L2.4 (1), U22.13 (0); also elsewhere on the board
0-: C15.2, L2.3, U21.13 (0); also elsewhere on the board
0V: C16.2, C21.2, C28.POS, D3.1 (A), D3.2 (C), R30.1, R35.1, R39.1, R45.1, R46.1, R69.2, TP8.1, U13.5 (+IN), U15.5 (+IN)
1+: C17.1, L3.4 (1), U22.14 (1); also elsewhere on the board
1-: C17.2, L3.3, U21.14 (1); also elsewhere on the board
2+: C20.1, L4.4 (1), U22.15 (2); also elsewhere on the board
2-: C20.2, L4.3, U21.15 (2); also elsewhere on the board
3+: C22.1, L5.4 (1), U22.12 (3); also elsewhere on the board
3-: C22.2, L5.3, U21.12 (3); also elsewhere on the board
4+: C24.1, L6.4 (1), U22.1 (4); also elsewhere on the board
4-: C24.2, L6.3, U21.1 (4); also elsewhere on the board
80_POWER: R73.2, TP11.1, U20.3 (EN)
!80_OE: U21.6 (EN), U22.6 (EN); also elsewhere on the board
!LOW_BAT: R65.1, R72.1, U19.1 (!RESET); also elsewhere on the board
AGND: C23.1, C25.2, C26.2, C27.2, C28.NEG, C29.2, C30.NEG, C31.2, C32.2, C33.2, C34.2, C35.2, C36.2, C37.2, C38.2, C39.2, L7.2 (4), R47.1, R56.1, R60.1, R61.1, R63.1, R64.1, R70.1, R71.1, TP10.1, U13.4 (V-), U14.4 (V-), U15.4 (V-), U16.3 (V-), U17.2 (V-), U18.6 (INH), U18.7 (GND), U18.8 (GND), U19.2 (GND), U20.2 (GND), U21.8 (V-), U22.8 (V-); also elsewhere on the board
AMP_0: U18.10 (A); also elsewhere on the board
AMP_1: U18.9 (B); also elsewhere on the board
BATT+: L7.4 (1), SW1.1 (NO); also elsewhere on the board
BATT-: CN6.3, CN6.4, L7.3; also elsewhere on the board
CH_0: U21.11 (A), U22.11 (A); also elsewhere on the board
CH_1: U21.10 (B), U22.10 (B); also elsewhere on the board
CH_2: U21.9 (C), U22.9 (C); also elsewhere on the board
COMP_80: R58.2; also elsewhere on the board
DGND: M1.CASE1; also elsewhere on the board
unnamed: R50.2, R51.1
unnamed: R39.2, R40.3
unnamed: CN5.1 (GND), R64.2
unnamed: R30.2, R31.1, U18.11 (3)
unnamed: R31.2, R32.1, U18.15 (2)
unnamed: R32.2, R33.1, U18.14 (1)
unnamed: R33.2, R34.1, U18.12 (0)
unnamed: C27.1, R68.1, R71.2, U14.5 (+IN)
unnamed: C19.2, R53.2, R54.1, U13.6 (-IN)
unnamed: U14.2 (-IN), U18.13 (COM)
unnamed: C13.2, R34.2, U14.1 (OUT)
unnamed: R43.2, R46.2, U14.3 (+IN)
unnamed: C19.1, R54.2, TP6.1, U13.7 (OUT), U16.10 (COM)
unnamed: R36.2, TP4.1, U13.1 (OUT), U16.6 (COM)
unnamed: R35.2, R36.1, U13.2 (-IN)
unnamed: C16.1, R38.2, R45.2, U13.3 (+IN)
unnamed: R57.1, U16.2 (NO)
unnamed: R55.1, U16.9 (NC)
unnamed: R55.2, R57.2, U21.3 (COM)
unnamed: R37.1, U16.7 (NC)
unnamed: R44.1, U16.4 (NO)
unnamed: R37.2, R44.2, U22.3 (COM)
unnamed: R40.1, R41.1
unnamed: C18.1, R41.2, R42.1, U15.1 (OUT)
unnamed: C14.2, R42.2, U15.6 (-IN)
unnamed: C14.1, R43.1, R52.2, TP7.1, U15.7 (OUT), U17.1 (-IN)
unnamed: R40.2, U15.2 (-IN)
unnamed: C21.1, R48.1, U15.3 (+IN)
unnamed: R48.2, R49.1
unnamed: C18.2, R49.2, R50.1
unnamed: D3.3 (AC), R51.2, R51.3, R52.1
unnamed: C13.1, R38.1, R53.1, TP5.1
unnamed: R69.1, U14.6 (-IN), U14.7 (OUT)
unnamed: R58.1, R59.1, R61.2, U17.3 (+IN)
unnamed: R59.2, R62.1, U17.4 (OUT)
unnamed: D4.C (K1), R72.2
unnamed: C26.1, U19.4 (CT)
unnamed: C25.1, R67.1, R70.2, U19.5 (SENSE)
unnamed: C38.1, U20.4 (NR)
unnamed: CN6.1, CN6.2, F2.1
unnamed: R66.1, R67.2
unnamed: CN1.2 (L), L2.1 (2)
unnamed: CN1.3 (R), L2.2 (4)
unnamed: CN2.2 (L), L3.1 (2)
unnamed: CN2.3 (R), L3.2 (4)
unnamed: CN3.2 (L), L4.1 (2)
unnamed: CN3.3 (R), L4.2 (4)
unnamed: CN4.2 (L), L5.1 (2)
unnamed: CN4.3 (R), L5.2 (4)
unnamed: CN5.2 (L), L6.1 (2)
unnamed: CN5.3 (R), L6.2 (4)
unnamed: CN4.1 (GND), R63.2
unnamed: CN3.1 (GND), R60.2
unnamed: CN2.1 (GND), R56.2
unnamed: CN1.1 (GND), R47.2
unnamed: F2.2, SW1.2 (C)
SYNC80: R62.2, TP9.1; also elsewhere on the board
VA+3V3: C23.2, C31.1, C32.1, C33.1, C34.1, C35.1, C36.1, C37.1, C39.1, D4.A (A1), R65.2, R68.2, U13.8 (V+), U14.8 (V+), U15.8 (V+), U16.8 (V+), U17.5 (V+), U18.16 (VCC), U20.5 (VO), U21.16 (V+), U22.16 (V+); also elsewhere on the board
VA+5: C29.1, C30.POS, L7.1 (2), R66.2, R73.1, U19.6 (VDD), U20.1 (VI); also elsewhere on the board
ZOUT: U16.1 (IN), U16.5 (IN); also elsewhere on the board

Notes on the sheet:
ANALOG part
OUTPUT CH SELECT
AMPLITUDE
ZOUT SELECT
Hi : 10k / Lo : 100k
0 0 : x1
0 1 : x2
1 0 : x5
1 1 : x10
LOW BATTERY INDICATOR(RED)
Vth = 4.79V +/- 2%
Vref=0.405V
Analog GND
Analog POWER CTRL
1.65V
Vh = +/- 41mV
Vbias
0.5Vo-p
80Hz
Active when EN=LOW
1Vo-p
EM-80D Marker coil driver
Fo: +/-6% ADJ
